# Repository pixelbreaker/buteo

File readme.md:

# Buteo

### A unibody split 30 key keyboard (23332 layout) with Cirque trackpad and encoder.

This is the first PCB I have ever designed, and it has been a really fun experience learning both KiCAD and Fusion 360.

I got the PCB made at JLCPCB, gerber files are in `buteo-mx/gerbers.zip`.

Case files (STLs and STEP) are also included.

I haven't written the firmware yet...

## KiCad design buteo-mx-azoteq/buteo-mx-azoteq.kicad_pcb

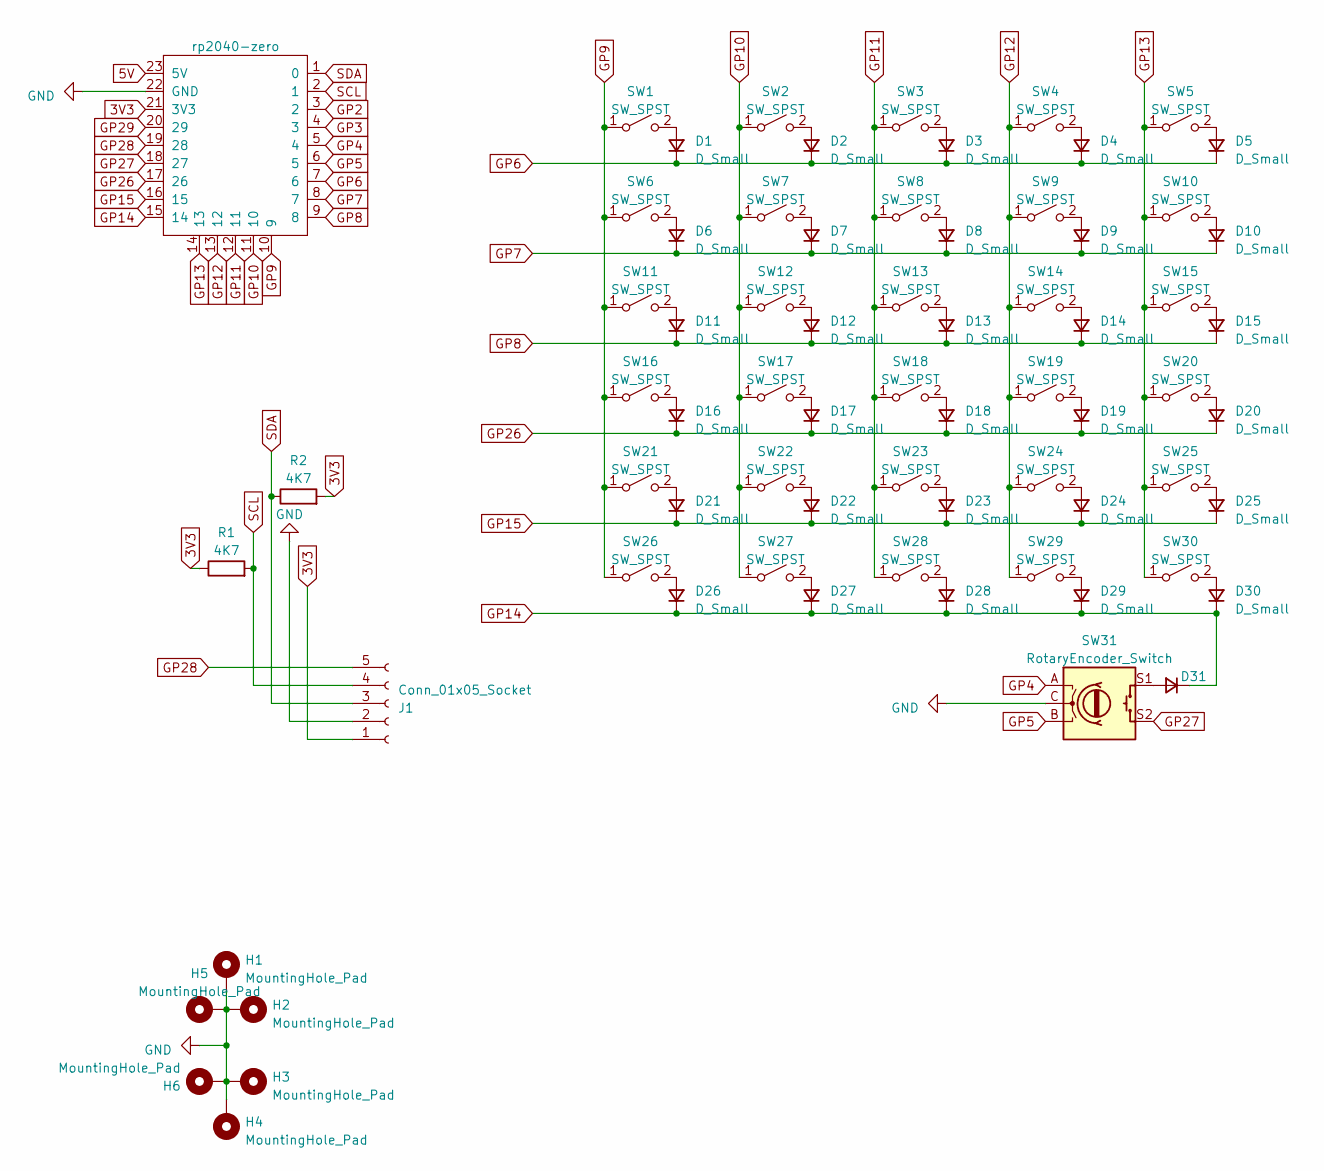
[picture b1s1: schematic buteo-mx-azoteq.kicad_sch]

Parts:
D1, D2, D3, D4, D5, D6, D7, D8, D9, D10, D11, D12, D13, D14, D15, D16, D17, D18, D19, D20, D21, D22, D23, D24, D25, D26, D27, D28, D29, D30, D31: D_Small; D_1206_3216Metric_Pad1.42x1.75mm_HandSolder
H1, H2, H3, H4, H5, H6: MountingHole_Pad; MountingHole_2.2mm_M2_ISO7380_Pad_TopBottom
J1: Conn_01x05_Socket; PinHeader_1x05_P2.54mm_Vertical
R1, R2: 4K7; R_1206_3216Metric_Pad1.30x1.75mm_HandSolder
RZ1: rp2040-zero; rp2040-zero-tht
SW1, SW2, SW3, SW4, SW5, SW6, SW7, SW8, SW9, SW10, SW11, SW12, SW13, SW14, SW15, SW16, SW17, SW18, SW19, SW20, SW21, SW22, SW23, SW24, SW25, SW26, SW27, SW28, SW29, SW30: SW_SPST; SW_Kailh_Choc_V1_1.00u_MX
SW31: RotaryEncoder_Switch; EVQWGD001

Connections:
3V3: J1.1, R1.1, R2.2, RZ1.21 (3V3)
5V: RZ1.23 (5V)
GND: H1.1, H2.1, H3.1, H4.1, H5.1, H6.1, J1.2, RZ1.22 (GND), SW31.C
GP2: RZ1.3 (2)
GP3: RZ1.4 (3)
GP4: RZ1.5 (4), SW31.A
GP5: RZ1.6 (5), SW31.B
GP6: D1.1 (K), D2.1 (K), D3.1 (K), D4.1 (K), D5.1 (K), RZ1.7 (6)
GP7: D6.1 (K), D7.1 (K), D8.1 (K), D9.1 (K), D10.1 (K), RZ1.8 (7)
GP8: D11.1 (K), D12.1 (K), D13.1 (K), D14.1 (K), D15.1 (K), RZ1.9 (8)
GP9: RZ1.10 (9), SW1.1 (A), SW6.1 (A), SW11.1 (A), SW16.1 (A), SW21.1 (A), SW26.1 (A)
GP10: RZ1.11 (10), SW2.1 (A), SW7.1 (A), SW12.1 (A), SW17.1 (A), SW22.1 (A), SW27.1 (A)
GP11: RZ1.12 (11), SW3.1 (A), SW8.1 (A), SW13.1 (A), SW18.1 (A), SW23.1 (A), SW28.1 (A)
GP12: RZ1.13 (12), SW4.1 (A), SW9.1 (A), SW14.1 (A), SW19.1 (A), SW24.1 (A), SW29.1 (A)
GP13: RZ1.14 (13), SW5.1 (A), SW10.1 (A), SW15.1 (A), SW20.1 (A), SW25.1 (A), SW30.1 (A)
GP14: D26.1 (K), D27.1 (K), D28.1 (K), D29.1 (K), D30.1 (K), D31.1 (K), RZ1.15 (14)
GP15: D21.1 (K), D22.1 (K), D23.1 (K), D24.1 (K), D25.1 (K), RZ1.16 (15)
GP26: D16.1 (K), D17.1 (K), D18.1 (K), D19.1 (K), D20.1 (K), RZ1.17 (26)
GP27: RZ1.18 (27), SW31.S2
GP28: J1.5, RZ1.19 (28)
GP29: RZ1.20 (29)
unnamed: D1.2 (A), SW1.2 (B)
unnamed: D2.2 (A), SW2.2 (B)
unnamed: D3.2 (A), SW3.2 (B)
unnamed: D4.2 (A), SW4.2 (B)
unnamed: D5.2 (A), SW5.2 (B)
unnamed: D6.2 (A), SW6.2 (B)
unnamed: D7.2 (A), SW7.2 (B)
unnamed: D8.2 (A), SW8.2 (B)
unnamed: D9.2 (A), SW9.2 (B)
unnamed: D10.2 (A), SW10.2 (B)
unnamed: D11.2 (A), SW11.2 (B)
unnamed: D12.2 (A), SW12.2 (B)
unnamed: D13.2 (A), SW13.2 (B)
unnamed: D14.2 (A), SW14.2 (B)
unnamed: D15.2 (A), SW15.2 (B)
unnamed: D16.2 (A), SW16.2 (B)
unnamed: D17.2 (A), SW17.2 (B)
unnamed: D18.2 (A), SW18.2 (B)
unnamed: D19.2 (A), SW19.2 (B)
unnamed: D20.2 (A), SW20.2 (B)
unnamed: D21.2 (A), SW21.2 (B)
unnamed: D22.2 (A), SW22.2 (B)
unnamed: D23.2 (A), SW23.2 (B)
unnamed: D24.2 (A), SW24.2 (B)
unnamed: D25.2 (A), SW25.2 (B)
unnamed: D26.2 (A), SW26.2 (B)
unnamed: D27.2 (A), SW27.2 (B)
unnamed: D28.2 (A), SW28.2 (B)
unnamed: D29.2 (A), SW29.2 (B)
unnamed: D30.2 (A), SW30.2 (B)
unnamed: D31.2 (A), SW31.S1
SCL: J1.4, R1.2, RZ1.2 (1)
SDA: J1.3, R2.1, RZ1.1 (0)

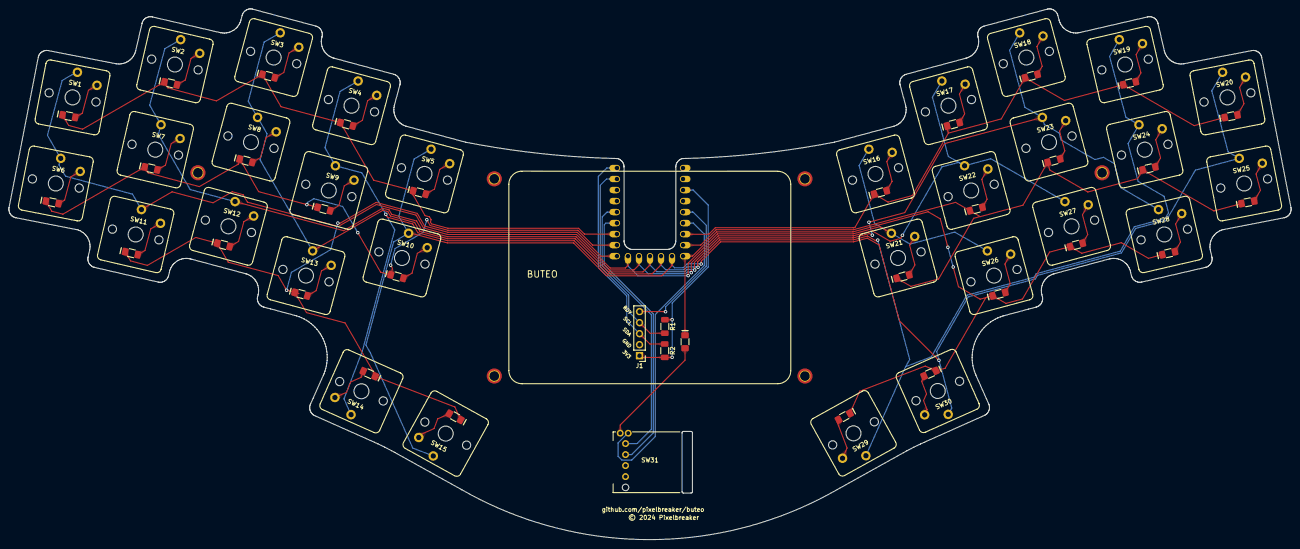
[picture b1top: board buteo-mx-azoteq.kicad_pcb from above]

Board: 2 copper layers, 295.6 x 122.4 mm, 72 parts (1 on the bottom side), 50 nets.

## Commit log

2023-08-07 Fix trackpad position
2023-08-09 MX version
2023-08-09 Fix footprint references and 3D models
2023-10-03 V1 MX
2023-10-04 readme
2023-10-04 typo
2023-10-04 clean house
2024-01-28 Add azoteq variant

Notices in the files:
buteo-mx-azoteq/buteo-mx-azoteq.kicad_pcb:
© 2024 Pixelbreaker
